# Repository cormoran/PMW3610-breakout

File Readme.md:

My PMW3610 breakout board collections and kicad library

- [V1](kicad_projects/PMW3610-breakout-v1/Readme.md)
  - Designed to minimize 1 side length (14mm x 21mm)
- [V2](kicad_projects/PMW3610-breakout-v2/Readme.md)
  - Designed to minimize width + height (17.6mm x 16.6mm)
  - Designed for 1 layer PCB assembly
  - 1.8V support by default. 3.6V support by manually soldering LDO.
- [V3](kicad_projects/PMW3610-breakout-v3/Readme.md) (I've not assembled yet!)
  - Designed to minimize width + height (17.6mm x 16.6mm)
  - Designed for 1 layer PCB assembly
  - 3.6V support by default. 1.8V support by removing LDO.

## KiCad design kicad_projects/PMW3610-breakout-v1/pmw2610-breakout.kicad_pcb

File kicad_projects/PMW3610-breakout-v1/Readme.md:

## PMW3610 breakout board (v1)

Features

- width = **14mm** (by cutting mounting holes)
- height = 21mm (by cutting mounting holes)
- 3.6V support
- 6pin 5mm pitch FFC

Problems

- Requires high manual soldering skills
- Unstable due to LDO's poor transient response?
  - It got stable by replacing C2 to 10uF in my case

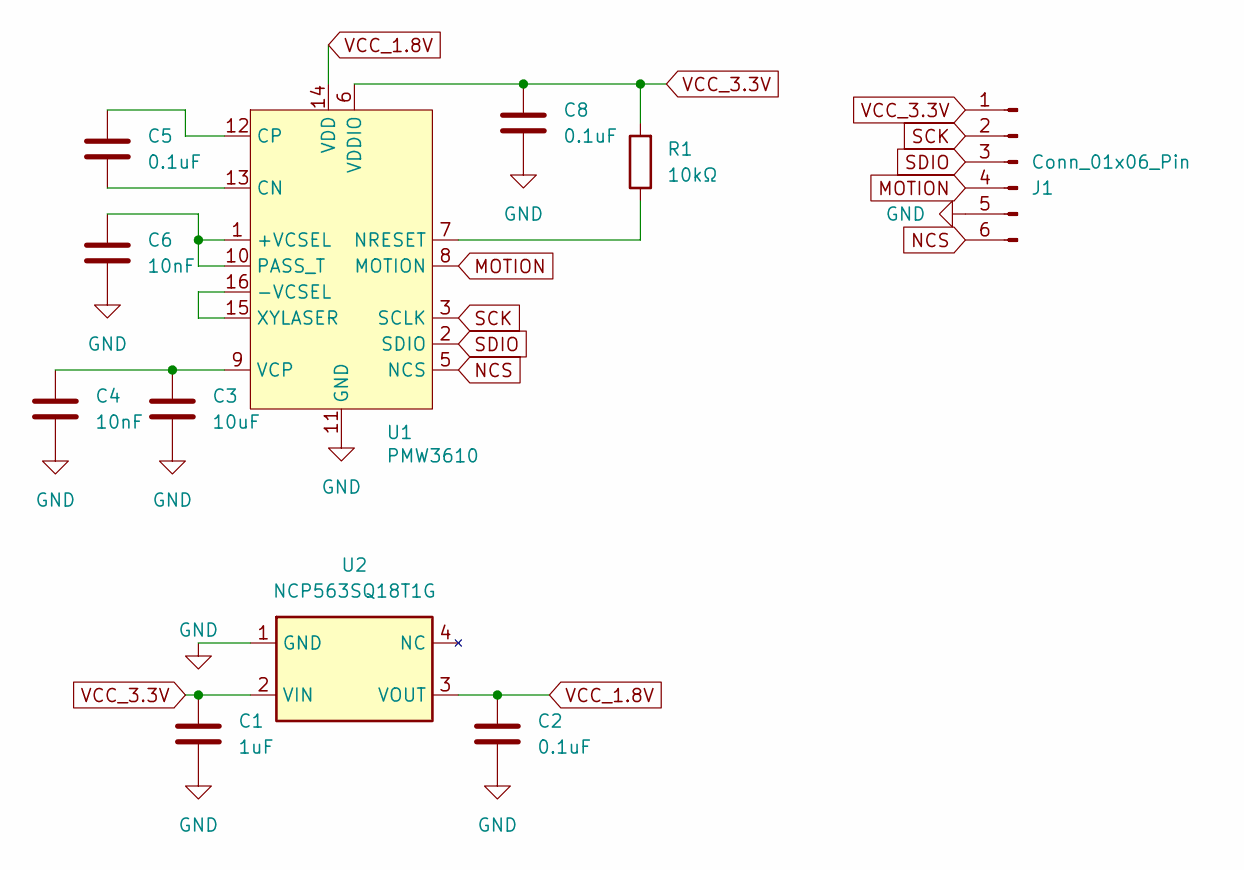
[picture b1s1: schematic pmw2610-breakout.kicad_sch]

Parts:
C1: 1uF; C_0805_2012Metric
C2, C5, C8: 0.1uF; C_0805_2012Metric
C3: 10uF; C_0805_2012Metric
C4, C6: 10nF; C_0805_2012Metric
J1: Conn_01x06_Pin; TE_0-1734839-6_1x06-1MP_P0.5mm_Horizontal
R1: 10kΩ; R_0805_2012Metric
U1: PMW3610; PMW3610DM-SUDU 16Pin
U2: NCP563SQ18T1G; SOT-343_SC-70-4

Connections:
GND: C1.2, C2.2, C3.2, C4.2, C6.2, C8.2, J1.5, U1.11 (GND), U2.1 (GND)
MOTION: J1.4, U1.8 (MOTION)
NCS: J1.6, U1.5 (NCS)
unnamed: C6.1, U1.1 (+VCSEL), U1.10 (PASS_T)
unnamed: U1.15 (XYLASER), U1.16 (-VCSEL)
unnamed: C5.2, U1.13 (CN)
unnamed: C5.1, U1.12 (CP)
unnamed: R1.1, U1.7 (NRESET)
unnamed: C3.1, C4.1, U1.9 (VCP)
SCK: J1.2, U1.3 (SCLK)
SDIO: J1.3, U1.2 (SDIO)
VCC_1.8V: C2.1, U1.14 (VDD), U2.3 (VOUT)
VCC_3.3V: C1.1, C8.1, J1.1, R1.2, U1.6 (VDDIO), U2.2 (VIN)

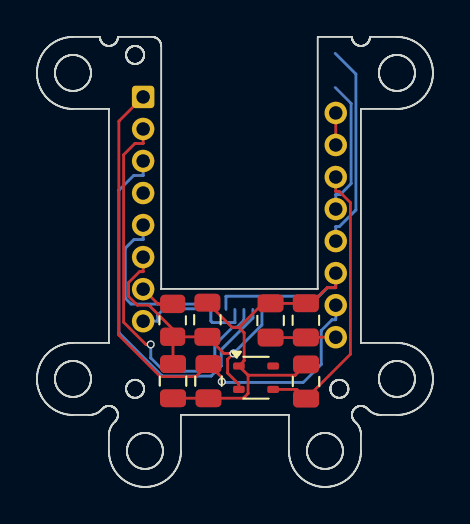
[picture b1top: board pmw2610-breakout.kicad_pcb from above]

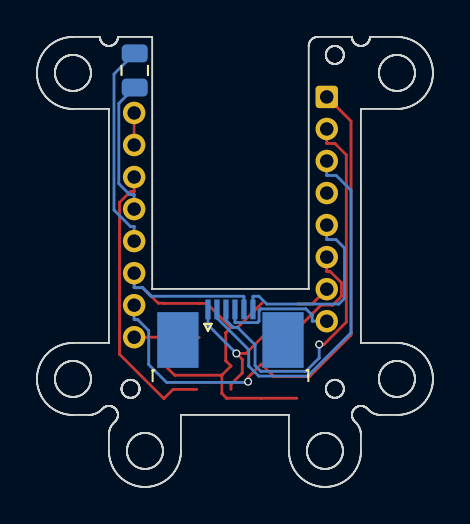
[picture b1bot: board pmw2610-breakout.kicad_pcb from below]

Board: 2 copper layers, 22.0 x 25.0 mm, 11 parts (2 on the bottom side), 13 nets.

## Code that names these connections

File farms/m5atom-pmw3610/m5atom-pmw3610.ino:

// This code is based on https://github.com/inorichi/zmk-pmw3610-driver
#include <M5Atom.h>

// M5Atom pin assignment

#define SCK G22
#define SDIO G19
#define MOTION G23
#define NCS G33

// --

#define T_NCS_SCLK 1     /* 120 ns (rounded to 1us) */
#define T_SCLK_NCS_WR 10 /* 10 us */
#define T_SRAD 4         /* 4 us */
#define T_SRAD_MOTBR 4   /* same as T_SRAD */
#define T_SRX 1          /* 250 ns (rounded to 1 us) */
#define T_SWX 30         /* SWW: 30 us, SWR: 20 us */
#define T_BEXIT 1        /* 250 ns (rounded to 1us)*/

/* Sensor registers (addresses) */
#define PMW3610_REG_PRODUCT_ID 0x00
#define PMW3610_REG_REVISION_ID 0x01
#define PMW3610_REG_MOTION 0x02
#define PMW3610_REG_DELTA_X_L 0x03
#define PMW3610_REG_DELTA_Y_L 0x04
#define PMW3610_REG_DELTA_XY_H 0x05
#define PMW3610_REG_SQUAL 0x06
#define PMW3610_REG_SHUTTER_HIGHER 0x07
#define PMW3610_REG_SHUTTER_LOWER 0x08
#define PMW3610_REG_PIX_MAX 0x09
#define PMW3610_REG_PIX_AVG 0x0A
#define PMW3610_REG_PIX_MIN 0x0B

#define PMW3610_REG_CRC0 0x0C
#define PMW3610_REG_CRC1 0x0D
#define PMW3610_REG_CRC2 0x0E
#define PMW3610_REG_CRC3 0x0F
#define PMW3610_REG_SELF_TEST 0x10

#define PMW3610_REG_PERFORMANCE 0x11
#define PMW3610_REG_MOTION_BURST 0x12

#define PMW3610_REG_RUN_DOWNSHIFT 0x1B
#define PMW3610_REG_REST1_PERIOD 0x1C
#define PMW3610_REG_REST1_DOWNSHIFT 0x1D
#define PMW3610_REG_REST2_PERIOD 0x1E
#define PMW3610_REG_REST2_DOWNSHIFT 0x1F
#define PMW3610_REG_REST3_PERIOD 0x20
#define PMW3610_REG_OBSERVATION 0x2D

#define PMW3610_REG_PIXEL_GRAB 0x35
#define PMW3610_REG_FRAME_GRAB 0x36

#define PMW3610_REG_POWER_UP_RESET 0x3A
#define PMW3610_REG_SHUTDOWN 0x3B

#define PMW3610_REG_SPI_CLK_ON_REQ 0x41
#define PMW3610_REG_RES_STEP 0x85

#define PMW3610_REG_NOT_REV_ID 0x3E
#define PMW3610_REG_NOT_PROD_ID 0x3F

#define PMW3610_REG_PRBS_TEST_CTL 0x47
#define PMW3610_REG_SPI_PAGE0 0x7F
#define PMW3610_REG_VCSEL_CTL 0x9E
#define PMW3610_REG_LSR_CONTROL 0x9F
#define PMW3610_REG_SPI_PAGE1 0xFF

/* Sensor identification values */
#define PMW3610_PRODUCT_ID 0x3E

/* Power-up register commands */
#define PMW3610_POWERUP_CMD_RESET 0x5A
#define PMW3610_POWERUP_CMD_WAKEUP 0x96

/* spi clock enable/disable commands */
#define PMW3610_SPI_CLOCK_CMD_ENABLE 0xBA
#define PMW3610_SPI_CLOCK_CMD_DISABLE 0xB5

/* write command bit position */
// #define BIT(i) (1 << i)
#define PMW3610_WRITE_BIT BIT(7)

CRGB dispColor(uint8_t g, uint8_t r, uint8_t b) {
    return (CRGB)((g << 16) | (r << 8) | b);
}

static void set_cs(bool cs) {
    if (!cs) {
        delayMicroseconds(T_NCS_SCLK);
    }
    digitalWrite(NCS, cs ? 0 : 1);
    if (cs) {
        delayMicroseconds(T_NCS_SCLK);
    }
}

static uint8_t reg_read(uint8_t reg_address) {
    set_cs(true);
    pinMode(SDIO, OUTPUT);
    for (int8_t i = 7; i >= 0; i--) {
        digitalWrite(SCK, 0);
        delayMicroseconds(1);
        digitalWrite(SDIO, reg_address & BIT(i));
        digitalWrite(SCK, 1);
        delayMicroseconds(5);
    }
    pinMode(SDIO, INPUT);
    delayMicroseconds(T_SRAD);
    delay(10);
    uint8_t r = 0;
    for (int8_t i = 7; i >= 0; i--) {
        digitalWrite(SCK, 0);
        delayMicroseconds(1);
        digitalWrite(SCK, 1);
        r |= digitalRead(SDIO) << i;
        delayMicroseconds(1);
    }
    set_cs(false);
    delayMicroseconds(T_SRX);
    return r;
}

static void _reg_write(uint8_t reg_address, uint8_t data) {
    reg_address |= PMW3610_WRITE_BIT;

    set_cs(true);
    pinMode(SDIO, OUTPUT);
    for (int8_t i = 7; i >= 0; i--) {
        digitalWrite(SCK, 0);
        digitalWrite(SDIO, reg_address & BIT(i));
        delayMicroseconds(1);
        digitalWrite(SCK, 1);
        delayMicroseconds(5);
    }
    for (int8_t i = 7; i >= 0; i--) {
        digitalWrite(SCK, 0);
        digitalWrite(SDIO, data & BIT(i));
        delayMicroseconds(1);
        digitalWrite(SCK, 1);
        delayMicroseconds(5);
    }
    delayMicroseconds(T_SCLK_NCS_WR);
    set_cs(false);
    delayMicroseconds(T_SWX);
}

static void reg_write(uint8_t reg_address, uint8_t data) {
    _reg_write(PMW3610_REG_SPI_CLK_ON_REQ, PMW3610_SPI_CLOCK_CMD_ENABLE);
    _reg_write(reg_address, data);
    _reg_write(PMW3610_REG_SPI_CLK_ON_REQ, PMW3610_SPI_CLOCK_CMD_DISABLE);
}

struct MotionData {
    bool motion;
    int16_t dx;
    int16_t dy;
};

void setup() {
    M5.begin(true, false, true);
    M5.dis.drawpix(0, dispColor(0, 0, 0));
    pinMode(SCK, OUTPUT);
    pinMode(SDIO, OUTPUT);
    pinMode(NCS, OUTPUT);
    pinMode(MOTION, INPUT);

    // Serial.begin(38400);
    init_pmw3610();
}

void init_pmw3610() {
    set_cs(false);
    set_cs(true);
    reg_write(PMW3610_REG_POWER_UP_RESET, PMW3610_POWERUP_CMD_RESET);

    delay(10);
    reg_write(PMW3610_REG_OBSERVATION, 0x00);

    delay(200);
    uint8_t obs = reg_read(PMW3610_REG_OBSERVATION);
    if ((obs & 0x0F) != 0x0F) {
        Serial.println("observation is wrong");
        return;
    }
    Serial.write("Product Id = ");
    Serial.println(reg_read(PMW3610_REG_PRODUCT_ID));
    Serial.write("Revision Id = ");
    Serial.println(reg_read(PMW3610_REG_REVISION_ID));

    delay(50);

    reg_read(PMW3610_REG_MOTION);
    reg_read(PMW3610_REG_DELTA_X_L);
    reg_read(PMW3610_REG_DELTA_Y_L);
    reg_read(PMW3610_REG_DELTA_XY_H);
}

void loop() {
    uint8_t motion = reg_read(PMW3610_REG_MOTION);
    if (motion & BIT(7)) {
        Serial.write("Motion = ");
        Serial.println(motion);
        Serial.write("delta_x = ");
        Serial.println(reg_read(PMW3610_REG_DELTA_X_L));
        Serial.write("delta_y = ");
        Serial.println(reg_read(PMW3610_REG_DELTA_Y_L));
        Serial.write("delta_xy = ");
        Serial.println(reg_read(PMW3610_REG_DELTA_XY_H));
    }
    delay(1000);
    M5.dis.drawpix(0, dispColor(255, 0, 0));
    delay(1000);
    M5.dis.drawpix(0, dispColor(0, 255, 0));
}

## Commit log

2025-01-23 Import kicad_library private repo
2025-01-23 Import PMW3610-breakout from private repo
2025-01-23 Import sample arduino farms
2025-01-23 Remove GPS info from pictures and re-commit :( * Add readme * Add PMW3610-breakout-v1 old version PCB * Add Readme and pictures. Rename PMW3610-breakout to PMW3610-breakout-v2
2025-01-24 Add implementation pictures
2025-01-24 Add v3 breakout which support 3.6V by default without additional SMT parts
2025-03-13 Fix missing wire in V3
2025-03-16 Add LICENSE
